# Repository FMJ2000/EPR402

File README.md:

# EPR402
Final year Computer Engineering Project source code repository. Project is to build an autonomous vacuum cleaner.

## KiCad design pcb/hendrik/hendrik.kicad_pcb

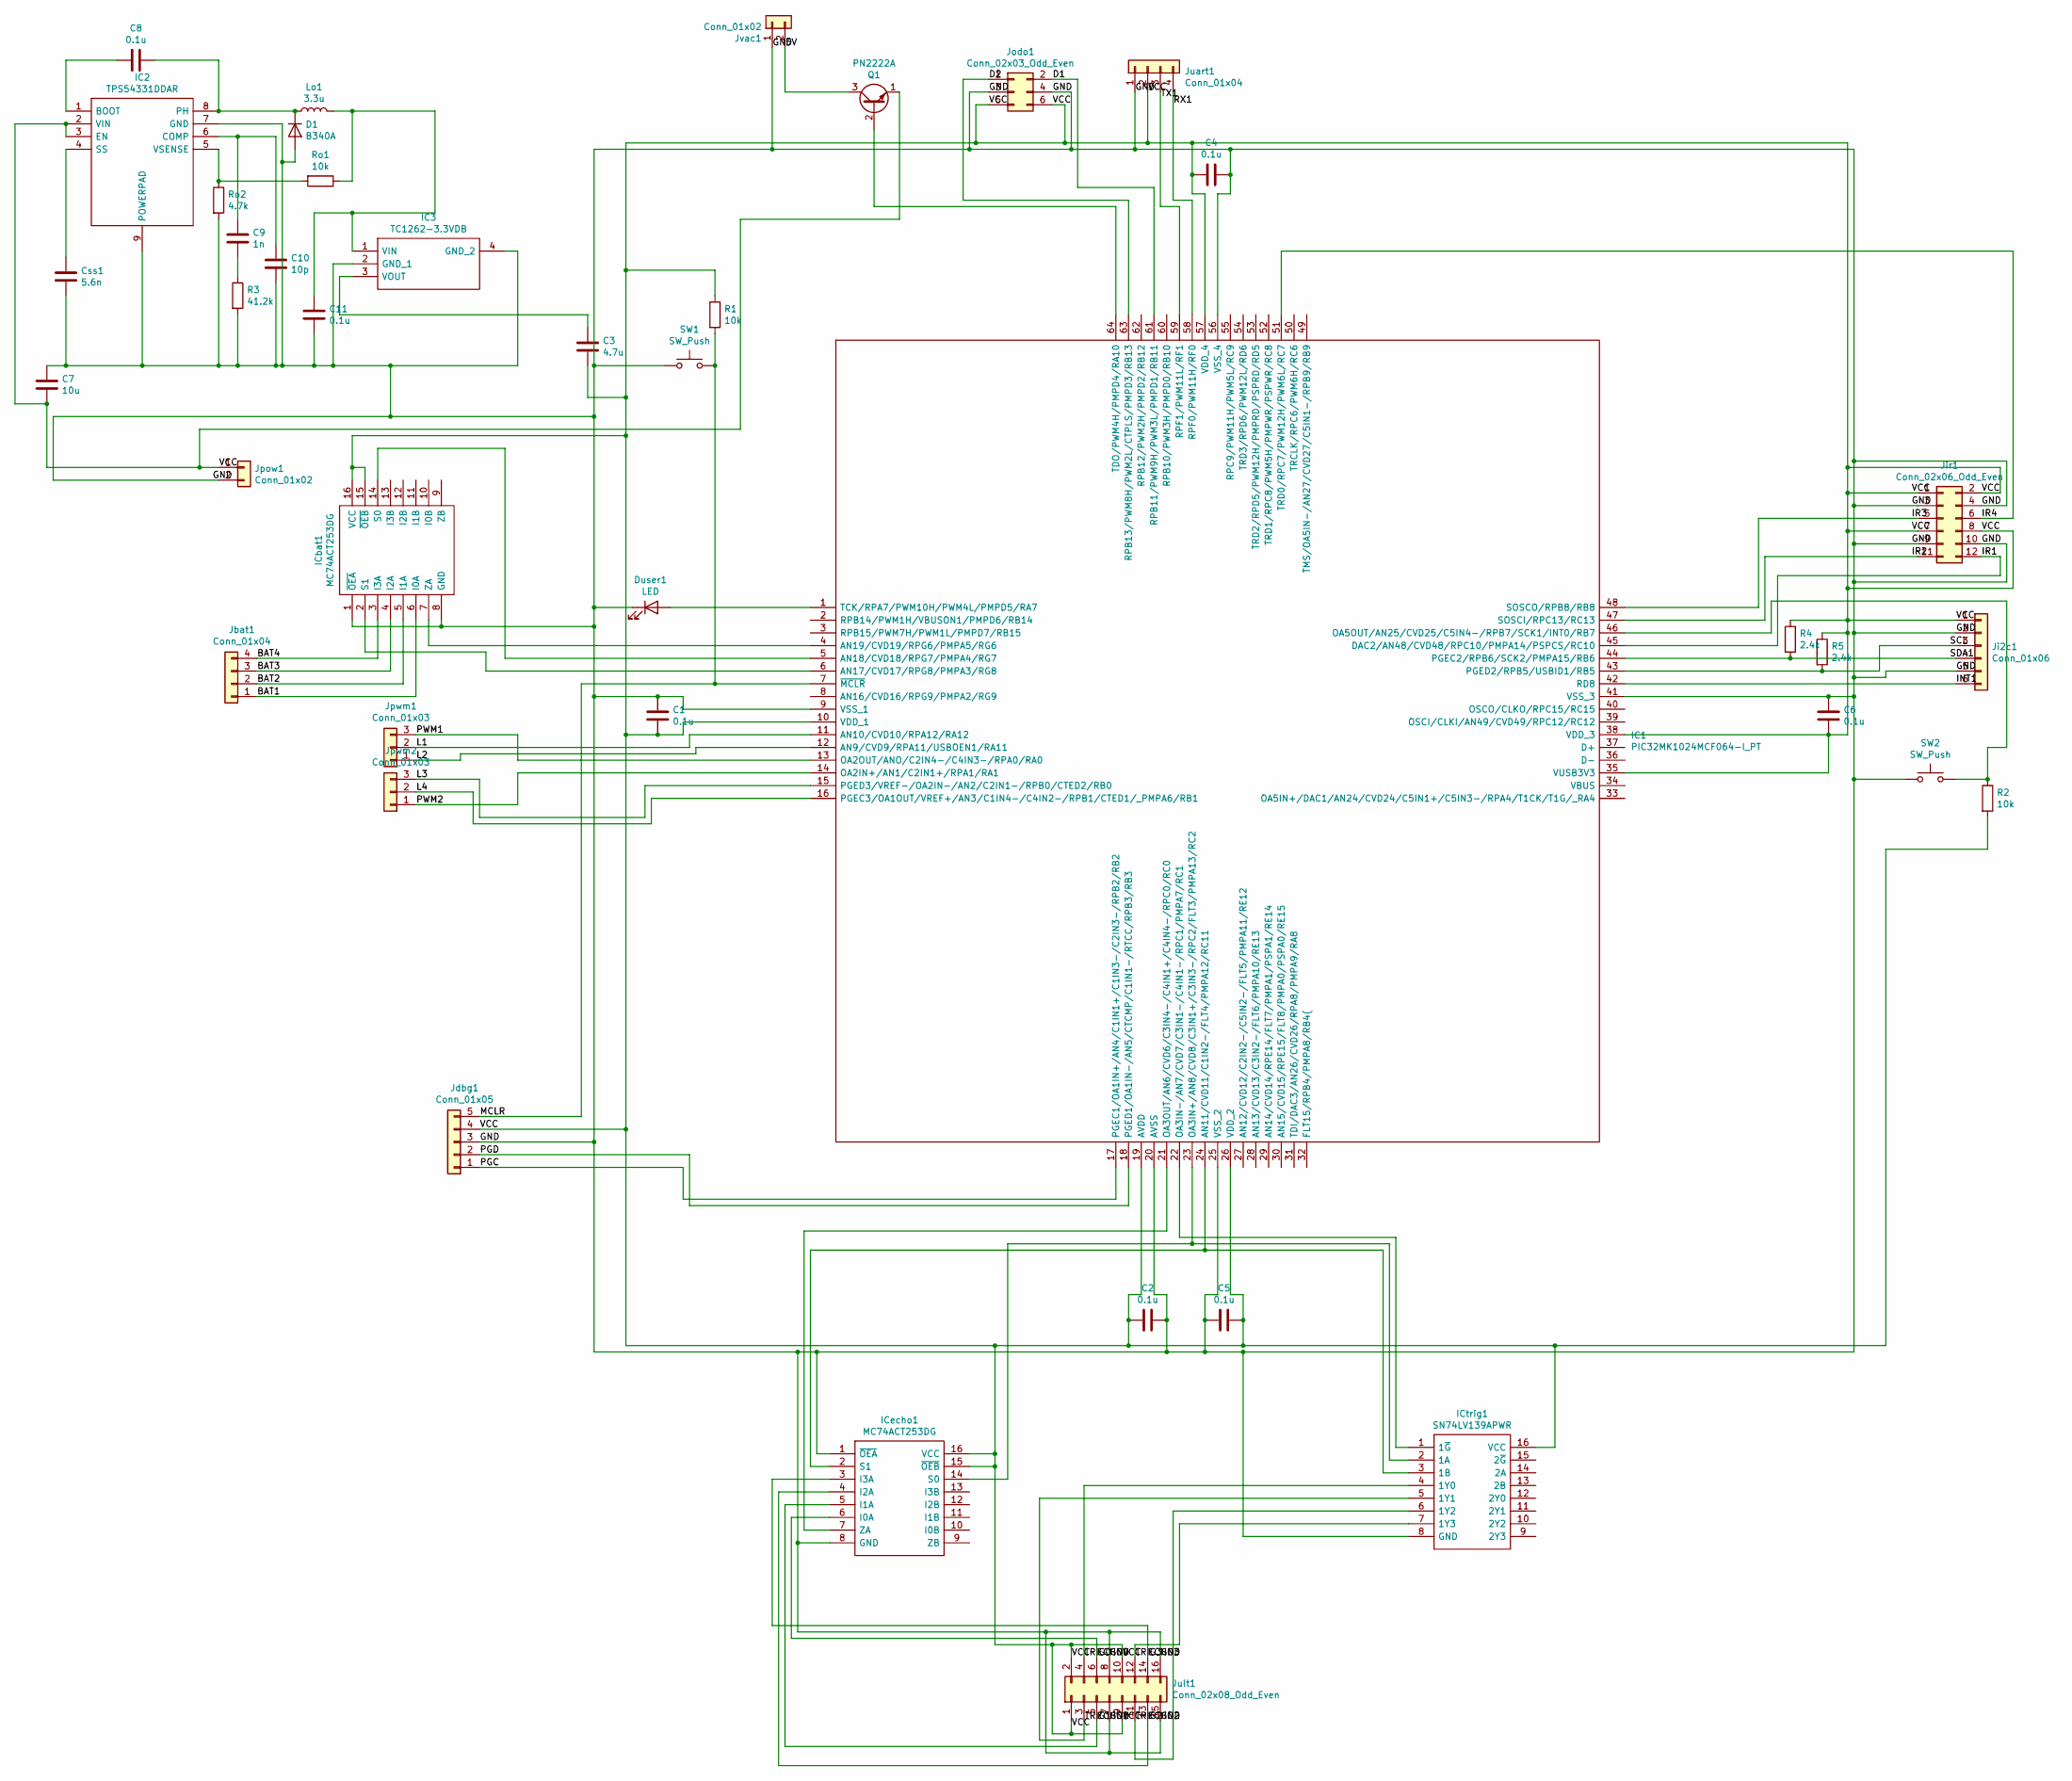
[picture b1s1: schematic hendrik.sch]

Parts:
C1, C2, C4, C5, C6, C8, C11: 0.1u; C_1206_3216Metric
C3: 4.7u; C_1206_3216Metric
C7: 10u; C_1206_3216Metric
C9: 1n; C_1206_3216Metric
C10: 10p; C_1206_3216Metric
Css1: 5.6n; C_1206_3216Metric
D1: B340A; D_SOD-123
Duser1: LED; LED_1206_3216Metric
IC1: PIC32MK1024MCF064-I_PT; TQFP-64_10x10mm_P0.5mm; Manufacturer_Part_Number PIC32MK1024MCF064-I/PT; Mouser Part Number 579-2MK1024MCF064IPT
IC2: TPS54331DDAR; TI_SO-PowerPAD-8; Manufacturer_Part_Number TPS54331DDAR; Mouser Part Number 595-TPS54331DDAR
IC3: TC1262-3.3VDB; SOT-223; Manufacturer_Part_Number TC1262-3.3VDB; Mouser Part Number 579-TC1262-3.3VDB
ICbat1: MC74ACT253DG; SOIC-16_3.9x9.9mm_P1.27mm; Manufacturer_Part_Number MC74ACT253DG
ICecho1: MC74ACT253DG; SOIC-16_3.9x9.9mm_P1.27mm; Manufacturer_Part_Number MC74ACT253DG
ICtrig1: SN74LV139APWR; TSSOP-16_4.4x5mm_P0.65mm; Manufacturer_Part_Number SN74LV139APWR; Mouser Part Number 595-SN74LV139APWR
Jbat1: Conn_01x04; PinHeader_1x04_P2.54mm_Vertical
Jdbg1: Conn_01x05; PinHeader_1x05_P2.54mm_Vertical
Ji2c1: Conn_01x06; PinHeader_1x06_P2.54mm_Vertical
Jir1: Conn_02x06_Odd_Even; PinHeader_2x06_P2.54mm_Vertical
Jodo1: Conn_02x03_Odd_Even; PinHeader_2x03_P2.54mm_Vertical
Jpow1: Conn_01x02; PinHeader_1x02_P2.54mm_Vertical
Jpwm1, Jpwm2: Conn_01x03; PinHeader_1x03_P2.54mm_Vertical
Juart1: Conn_01x04; PinHeader_1x04_P2.54mm_Vertical
Jult1: Conn_02x08_Odd_Even; PinHeader_2x08_P2.54mm_Vertical
Jvac1: Conn_01x02; PinHeader_1x02_P2.54mm_Vertical
Lo1: 3.3u; L_1210_3225Metric
Q1: PN2222A; TO-92_Inline
R1, R2: 10k; R_1206_3216Metric
R3: 41.2k; R_1206_3216Metric
R4, R5: 2.4k; R_1206_3216Metric
Ro1: 10k; R_1206_3216Metric
Ro2: 4.7k; R_1206_3216Metric
SW1, SW2: SW_Push; SW_PUSH_6mm

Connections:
/5V: Jvac1.2, Q1.3 (C)
/BAT1: ICbat1.6 (I0A), Jbat1.1
/BAT2: ICbat1.5 (I1A), Jbat1.2
/BAT3: ICbat1.4 (I2A), Jbat1.3
/BAT4: ICbat1.3 (I3A), Jbat1.4
/D1: IC1.61 (RPB11/PWM9H/PWM3L/PMPD1/RB11), Jodo1.2
/D2: IC1.63 (RPB13/PWM8H/PWM2L/CTPLS/PMPD3/RB13), Jodo1.1
/ECHO0: ICecho1.6 (I0A), Jult1.6
/ECHO1: ICecho1.5 (I1A), Jult1.5
/ECHO2: ICecho1.4 (I2A), Jult1.13
/ECHO3: ICecho1.3 (I3A), Jult1.14
/GND: C1.1, C2.1, C4.1, C5.2, C6.1, C7.1, C10.2, C11.2, Css1.2, D1.2 (A), Duser1.1 (K), IC1.9 (VSS_1), IC1.20 (AVSS), IC1.25 (VSS_2), IC1.41 (VSS_3), IC1.56 (VSS_4), IC2.7 (GND), IC2.9 (POWERPAD), IC3.2 (GND_1), IC3.4 (GND_2), ICbat1.1 (~OEA), ICbat1.8 (GND), ICecho1.1 (~OEA), ICecho1.8 (GND), ICtrig1.8 (GND), Jdbg1.3, Ji2c1.2, Ji2c1.5, Jir1.3, Jir1.4, Jir1.9, Jir1.10, Jodo1.3, Jodo1.4, Jpow1.2, Juart1.1, Jult1.7, Jult1.8, Jult1.15, Jult1.16, Jvac1.1, R3.2, Ro2.2, SW1.1, SW2.1; also elsewhere on the board
/INT1: IC1.42 (RD8), Ji2c1.6
/IR1: IC1.45 (DAC2/AN48/CVD48/RPC10/PMPA14/PSPCS/RC10), Jir1.12
/IR2: IC1.47 (SOSCI/RPC13/RC13), Jir1.11
/IR3: IC1.48 (SOSCO/RPB8/RB8), Jir1.5
/IR4: IC1.51 (TRD0/RPC7/PWM12H/PWM6L/RC7), Jir1.6
/L1: IC1.11 (AN10/CVD10/RPA12/RA12), Jpwm1.2
/L2: IC1.12 (AN9/CVD9/RPA11/USBOEN1/RA11), Jpwm1.1
/L3: IC1.15 (PGED3/VREF-/OA2IN-/AN2/C2IN1-/RPB0/CTED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), Jpwm2.3
/L4: IC1.16 (PGEC3/OA1OUT/VREF+/AN3/C1IN4-/C4IN2-/RP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), Jpwm2.2
/MCLR: IC1.7 (~MCLR), Jdbg1.5, R1.2, SW1.2; also elsewhere on the board
/PGC: IC1.17 (PGEC1/OA1IN+/AN4/C1IN1+/C1IN3-/C2IN3-/R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), Jdbg1.1
/PGD: IC1.18 (PGED1/OA1IN-/AN5/CTCMP/C1IN1-/RTCC/RPB3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), Jdbg1.2
/PWM1: IC1.13 (OA2OUT/ANO/C2IN4-/C4IN3-/RPA0/RA0), Jpwm1.3
/PWM2: IC1.14 (OA2IN+/AN1/C2IN1+/RPA1/RA1), Jpwm2.1
/RX1: IC1.58 (RPF0/PWM11H/RF0), Juart1.4
/SCL: IC1.43 (PGED2/RPB5/USBID1/RB5), Ji2c1.3, R5.2
/SDA1: IC1.44 (PGEC2/RPB6/SCK2/PMPA15/RB6), Ji2c1.4, R4.2
/TRIG0: ICtrig1.4 (1Y0), Jult1.4
/TRIG1: ICtrig1.5 (1Y1), Jult1.3
/TRIG2: ICtrig1.6 (1Y2), Jult1.11
/TRIG3: ICtrig1.7 (1Y3), Jult1.12
/TX1: IC1.59 (RPF1/PWM11L/RF1), Juart1.3
/VCC: C1.2, C2.2, C3.2, C4.2, C5.1, C6.2, C7.2, IC1.10 (VDD_1), IC1.19 (AVDD), IC1.26 (VDD_2), IC1.35 (VUSB3V3), IC1.38 (VDD_3), IC1.57 (VDD_4), IC2.2 (VIN), IC2.3 (EN), ICbat1.15 (~OEB), ICbat1.16 (VCC), ICecho1.15 (~OEB), ICecho1.16 (VCC), ICtrig1.16 (VCC), Jdbg1.4, Ji2c1.1, Jir1.1, Jir1.2, Jir1.7, Jir1.8, Jodo1.5, Jodo1.6, Jpow1.1, Juart1.2, Jult1.1, Jult1.2, Jult1.9, Jult1.10, Q1.1 (E), R1.1, R2.2, R4.1, R5.1
unnamed: C3.1, IC3.3 (VOUT)
unnamed: C8.1, D1.1 (K), IC2.8 (PH), Lo1.1
unnamed: C8.2, IC2.1 (BOOT)
unnamed: C9.2, R3.1
unnamed: C9.1, C10.1, IC2.6 (COMP)
unnamed: C11.1, IC3.1 (VIN), Lo1.2, Ro1.1
unnamed: Css1.1, IC2.4 (SS)
unnamed 42: Duser1.2 (A), IC1.1 (TCK/RPA7/PWM10H/PWM4L/PMPD5/RA7); also elsewhere on the board
unnamed: IC1.4 (AN19/CVD19/RPG6/PMPA5/RG6), ICbat1.7 (ZA)
unnamed: IC1.5 (AN18/CVD18/RPG7/PMPA4/RG7), ICbat1.14 (S0)
unnamed: IC1.6 (AN17/CVD17/RPG8/PMPA3/RG8), ICbat1.2 (S1)
unnamed: IC1.21 (OA3OUT/AN6/CVD6/C3IN4-/C4IN1+/C4IN4-/RP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), ICecho1.7 (ZA)
unnamed: IC1.22 (OA3IN-/AN7/CVD7/C3IN1-/C4IN1-/RPC1/PMPA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), ICtrig1.1 (1~G)
unnamed: IC1.23 (OA3IN+/AN8/CVD8/C3IN1+/C3IN3-/RPC2/FLT3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), ICecho1.14 (S0), ICtrig1.2 (1A)
unnamed: IC1.24 (AN11/CVD11/C1IN2-/FLT4/PMPA12/RC11), ICecho1.2 (S1), ICtrig1.3 (1B)
unnamed 65: IC1.46 (OA5OUT/AN25/CVD25/C5IN4-/RPB7/SCK1/INT0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), R2.1, SW2.2; also elsewhere on the board
unnamed: IC1.64 (TDO/PWM4H/PMPD4/RA10), Q1.2 (B)
unnamed: IC2.5 (VSENSE), Ro1.2, Ro2.1

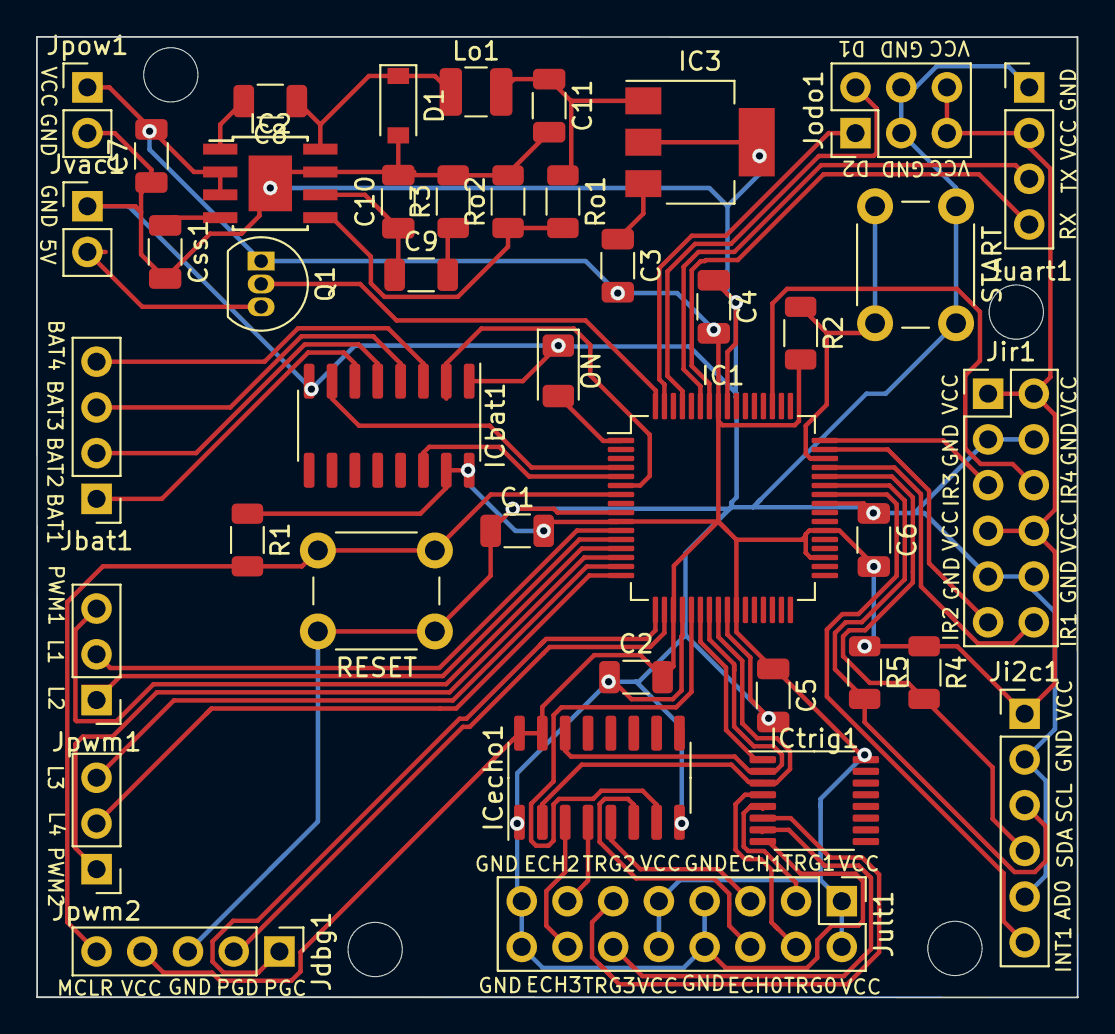
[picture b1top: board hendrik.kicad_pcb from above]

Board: 2 copper layers, 57.8 x 53.4 mm, 42 parts (0 on the bottom side), 53 nets.

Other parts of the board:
ON: LED; LED_1206_3216Metric
RESET: SW_Push; SW_PUSH_6mm
START: SW_Push; SW_PUSH_6mm

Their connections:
/GND: ON.1, RESET.1, START.1; also elsewhere on the board
/MCLR: RESET.2; also elsewhere on the board
unnamed 42: ON.2; also elsewhere on the board
unnamed 65: START.2; also elsewhere on the board

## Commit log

2021-04-22 simple simulated mapping
2021-05-06 bot C code added
2021-07-04 name change to correct title
2021-07-04 ultrasonic code v1
2021-07-05 ledger
2021-07-16 hendrik pt 1
2021-07-16 hendrik sensing
2021-07-16 obstacles
2021-07-17 survey
2021-07-17 survey 2
2021-07-18 refactoring
2021-08-24 New work
2021-08-24 PCB complete
2021-09-24 mplab init
2021-09-25 I2C working
2021-09-27 i2c slave works
2021-10-06 peripherals initialized
2021-10-07 pid controller
2021-10-07 basic navigation
2021-10-14 mapping and pid simulations
2021-10-20 position
2021-10-21 positioning
2021-10-22 local maps
2021-10-22 local mapping
2021-10-22 navigate submaps
2021-10-23 srt 2
2021-10-23 optimized mapping 1
2021-10-29 oled
2021-10-31 missing files
2021-11-05 display map
2021-11-05 complex working
2021-11-07 navigation working
2021-11-09 remove waste
2021-11-10 optimization
2021-11-12 srt pt1
2021-11-14 occupancy map
2021-11-15 ukf/2
2021-11-16 node queues
2021-11-16 latex report
2021-11-18 a_start
2021-11-18 pid working almost
2021-11-19 pid still not working, but almost
2021-11-19 mapping code
2021-11-19 positioning works!
2021-11-19 path planning 80 percent
2021-11-20 path planning test
2021-11-21 planner works!
2021-11-21 integration test complete
2021-12-02 new explorer
2021-12-02 almost ready
2021-12-03 anyday now
2021-12-04 map demo
2021-12-06 finished
